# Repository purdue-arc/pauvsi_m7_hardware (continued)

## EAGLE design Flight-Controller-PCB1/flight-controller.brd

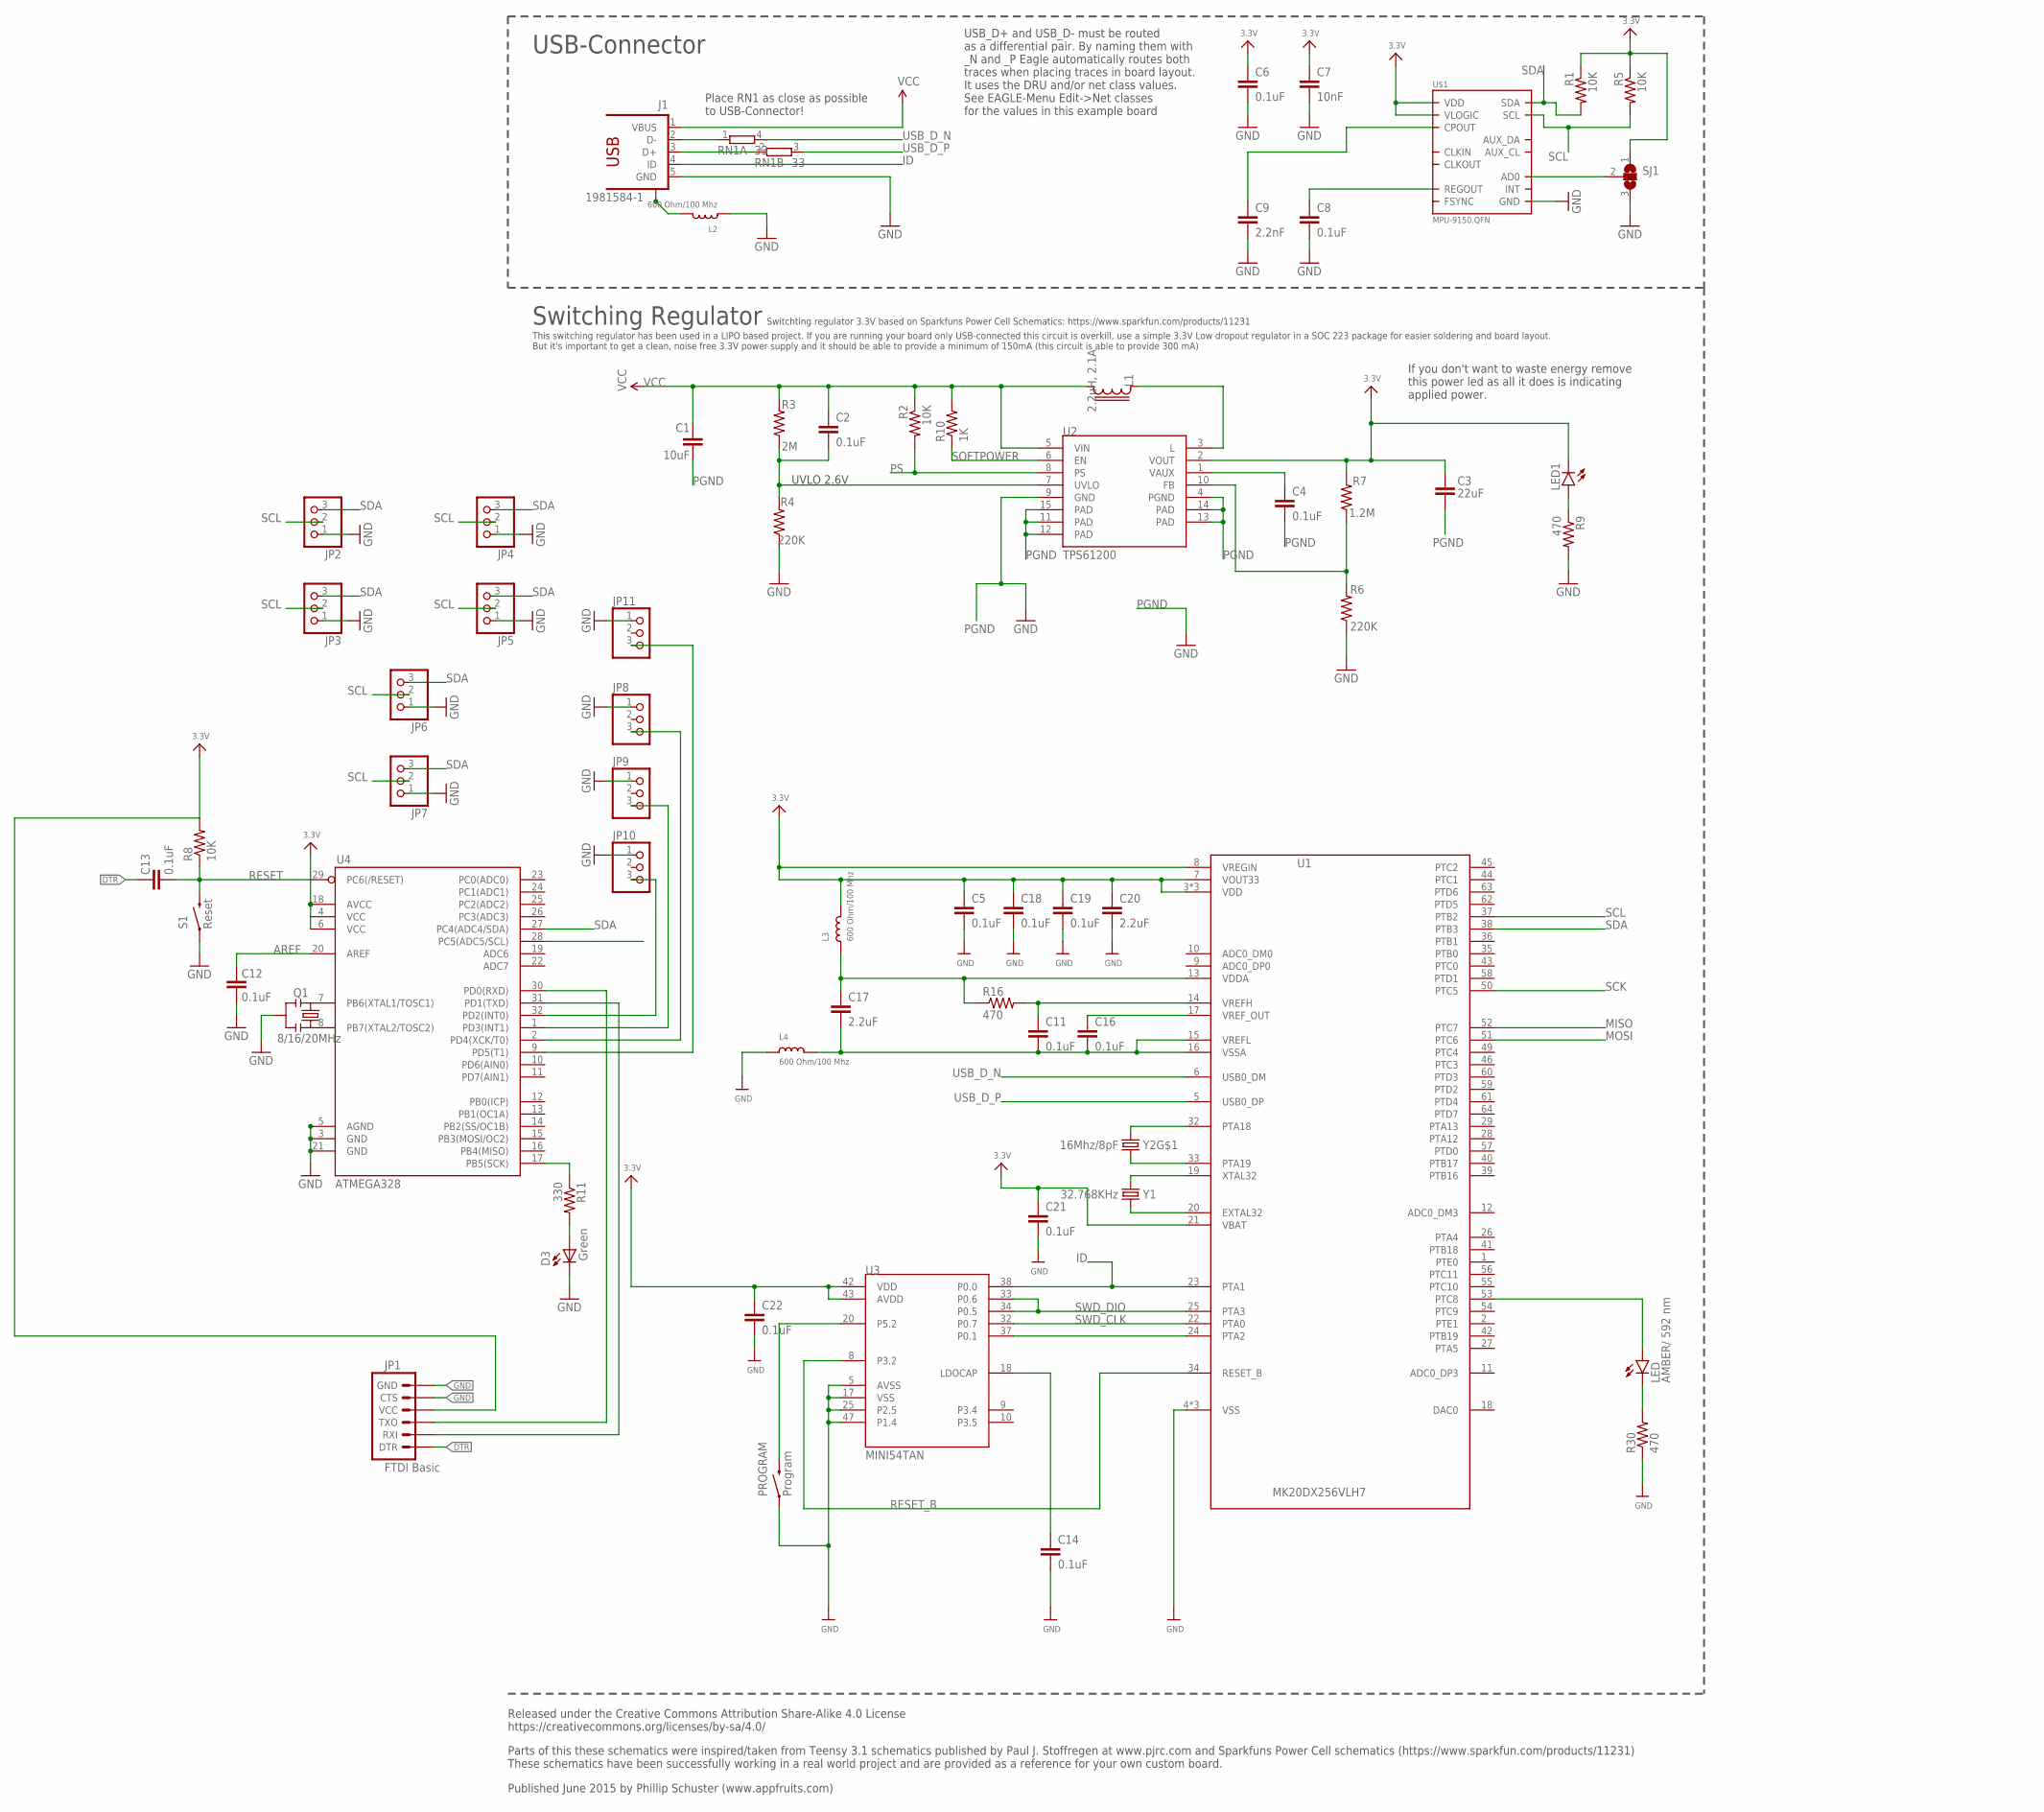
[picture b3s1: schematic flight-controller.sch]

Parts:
C1: 10uF; 0603-CAP
C2, C4, C5, C6, C8, C11, C12, C13, C14, C16, C18, C19, C21, C22: 0.1uF; 0603-CAP
C3: 22uF; 0603-CAP
C7: 10nF; 0603-CAP
C9: 2.2nF; 0603-CAP
C17, C20: 2.2uF; 0603-CAP
D3: Green; 0603-LED-ALT1
J1: 1981584-1; MPN ZX62-AB-5PA(11)
JP1: FTDI Basic; 1X06
JP2, JP3, JP4, JP5, JP6, JP7, JP8, JP9, JP10, JP11: PINHD-1X3; 1X03
L1: 2.2uH, 2.1A; LPS3015
L2, L3, L4: 600 Ohm/100 Mhz; 0805
LED: AMBER/ 592 nm; LED-0603
LED1: LED-GREEN; LED-0603
PROGRAM: Program; TACTILE-SWITCH-1101NE; MPN RS-282G05A3-SM RT
Q1: 8/16/20MHz; RESONATOR-SMD-1:1
R1, R2, R5, R8: 10K; 0603-RES
R3: 2M; 0603-RES
R4, R6: 220K; 0603-RES
R7: 1.2M; 0603-RES
R9, R16, R30: 470; 0603-RES
R10: 1K; 0603-RES
R11: 330; 0603-RES
RN1: 33; EXB34V; MPN EXB-34V330JV
S1: Reset; TACTILE-SWITCH-SMD-ALT01
SJ1: SJ2W; SJ_2
U1: MK20DX256VLH7; MPN MK20DX256VLH7
U2: TPS61200; QFN-10_PAD
U3: MINI54TAN
U4: ATMEGA328; TQFP32-08
U$1: MPU-9150.QFN; QFN.24.4X4
Y1: 32.768KHz; CRYSTAL-TXC-7A; MPN FC-255 32.7680K-A3
Y2: 16Mhz/8pF; CRYSTAL-SMD-5X3; MPN ECS-160-8-30B-CKM

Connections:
3.3V: C3.1, C5.1, C6.1, C7.1, C18.1, C19.1, C20.1, C21.1, C22.1, JP1.4 (VCC), L3.2, LED1.C, R1.1, R5.1, R7.2, R8.2, SJ1.1, U1.3 (VDD), U1.7 (VOUT33), U1.8 (VREGIN), U1.21 (VBAT), U1.30 (VDD), U1.48 (VDD), U2.2 (VOUT), U3.42 (VDD), U3.43 (AVDD), U4.4 (VCC), U4.6 (VCC), U4.18 (AVCC), U$1.3 (VDD), U$1.8 (VLOGIC), U$1.13 (VDD)
AREF: C12.2, U4.20 (AREF)
DTR: C13.2, JP1.1 (DTR)
FB: R6.2, R7.1, U2.10 (FB)
GND: C5.2, C6.2, C7.2, C8.2, C9.2, C12.1, C14.2, C18.2, C19.2, C20.2, C21.2, C22.2, D3.C, J1.5 (GND), JP1.5 (CTS), JP1.6 (GND), JP2.1, JP3.1, JP4.1, JP5.1, JP6.1, JP7.1, JP8.1, JP9.1, JP10.1, JP11.1, L2.1, L4.1, PROGRAM.P$1 (1), Q1.2, R4.1, R6.1, R9.2, R30.1, S1.1, S1.2 (1), SJ1.3, U1.4 (VSS), U1.31 (VSS), U1.47 (VSS), U3.5 (AVSS), U3.17 (VSS), U3.25 (P2.5), U3.47 (P1.4), U4.3 (GND), U4.5 (AGND), U4.21 (GND), U$1.15 (GND), U$1.17 (GND), U$1.18 (GND)
ID: J1.4 (ID), U1.23 (PTA1), U3.38 (P0.0)
MISO: U1.52 (PTC7)
MOSI: U1.51 (PTC6)
unnamed: LED1.A, R9.1
unnamed: L1.1, U2.3 (L)
unnamed: C9.1, U$1.20 (CPOUT)
unnamed: C8.1, U$1.10 (REGOUT)
unnamed: SJ1.2, U$1.9 (AD0)
unnamed: Q1.3, U4.8 (PB7(XTAL2/TOSC2))
unnamed: D3.A, R11.2
unnamed: Q1.1, U4.7 (PB6(XTAL1/TOSC1))
unnamed: JP1.3 (TXO), U4.30 (PD0(RXD))
unnamed: JP1.2 (RXI), U4.31 (PD1(TXD))
unnamed: JP10.3, U4.32 (PD2(INT0))
unnamed: LED.A, U1.53 (PTC8)
unnamed: JP9.3, U4.1 (PD3(INT1))
unnamed: JP8.3, U4.2 (PD4(XCK/T0))
unnamed: U1.24 (PTA2), U3.37 (P0.1)
unnamed: JP11.3, U4.9 (PD5(T1))
unnamed: LED.C, R30.2
unnamed: PROGRAM.P$2 (2), U3.20 (P5.2)
unnamed: C14.1, U3.18 (LDOCAP)
unnamed: U1.32 (PTA18), Y2.3 (2)
unnamed: U1.33 (PTA19), Y2.1
unnamed: U1.19 (XTAL32), Y1.P$2 (2)
unnamed: U1.20 (EXTAL32), Y1.P$1 (1)
NONE: R11.1, U4.17 (PB5(SCK))
PGND: C1.2, C3.2, C4.2, U2.4 (PGND), U2.9 (GND), U2.11 (PAD), U2.12 (PAD), U2.13 (PAD), U2.14 (PAD), U2.15 (PAD)
PS: R2.2, U2.8 (PS)
RESET: C13.1, R8.1, S1.3 (2), S1.4 (2), U4.29 (PC6(/RESET))
RESET_B: U1.34 (RESET_B), U3.8 (P3.2)
SCK: U1.50 (PTC5)
SCL: JP2.2, JP3.2, JP4.2, JP5.2, JP6.2, JP7.2, R5.2, U1.37 (PTB2), U4.28 (PC5(ADC5/SCL)), U$1.23 (SCL)
SDA: JP2.3, JP3.3, JP4.3, JP5.3, JP6.3, JP7.3, R1.2, U1.38 (PTB3), U4.27 (PC4(ADC4/SDA)), U$1.24 (SDA)
SOFTPOWER: R10.1, U2.6 (EN)
SWD_CLK: U1.22 (PTA0), U3.32 (P0.7)
SWD_DIO: U1.25 (PTA3), U3.33 (P0.6), U3.34 (P0.5)
USB_CON_N: J1.2 (D-), RN1.1
USB_CON_P: J1.3 (D+), RN1.2 (1)
USB_D_N: RN1.4 (2), U1.6 (USB0_DM)
USB_D_P: RN1.3 (2), U1.5 (USB0_DP)
USB_SHIELD: J1.S1, J1.S2, J1.S3, J1.S4, L2.2
UVLO: C2.2, R3.1, R4.2, U2.7 (UVLO)
VAUX: C4.1, U2.1 (VAUX)
VCC: C1.1, C2.1, J1.1 (VBUS), L1.2, R2.1, R3.2, R10.2, U2.5 (VIN)
VDDA: C17.1, L3.1, R16.1, U1.13 (VDDA)
VREFH: C11.1, R16.2, U1.14 (VREFH)
VREFL: C11.2, C16.2, C17.2, L4.2, U1.15 (VREFL), U1.16 (VSSA)
VREF_OUT: C16.1, U1.17 (VREF_OUT)

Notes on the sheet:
UVLO 2.6V
USB-Connector
Switching Regulator
Place RN1 as close as possible to USB-Connector!
If you don't want to waste energy remove this power led as all it does is indicating applied power.
USB_D+ and USB_D- must be routed as a differential pair. By naming them with _N and _P Eagle automatically routes both traces when placing traces in board layout. It uses the DRU and/or net class values. See EAGLE-Menu Edit->Net classes for the values in this example board
Released under the Creative Commons Attribution Share-Alike 4.0 License https://creativecommons.org/licenses/by-sa/4.0/
Parts of this these schematics were inspired/taken from Teensy 3.1 schematics published by Paul J. Stoffregen at www.pjrc.com and Sparkfuns Power Cell schematics (https://www.sparkfun.com/products/11231) These schematics have been successfully working in a real world project and are provided as a r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
Published June 2015 by Phillip Schuster (www.appfruits.com)
Switchting regulator 3.3V based on Sparkfuns Power Cell Schematics: https://www.sparkfun.com/products/11231
This switching regulator has been used in a LIPO based project. If you are running your board only USB-connected this circuit is overkill, use a simple 3.3V Low dropout regulator in a SOC 223 package for easier soldering and board layout. But it's important to get a clean, noise free 3.3V power sup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

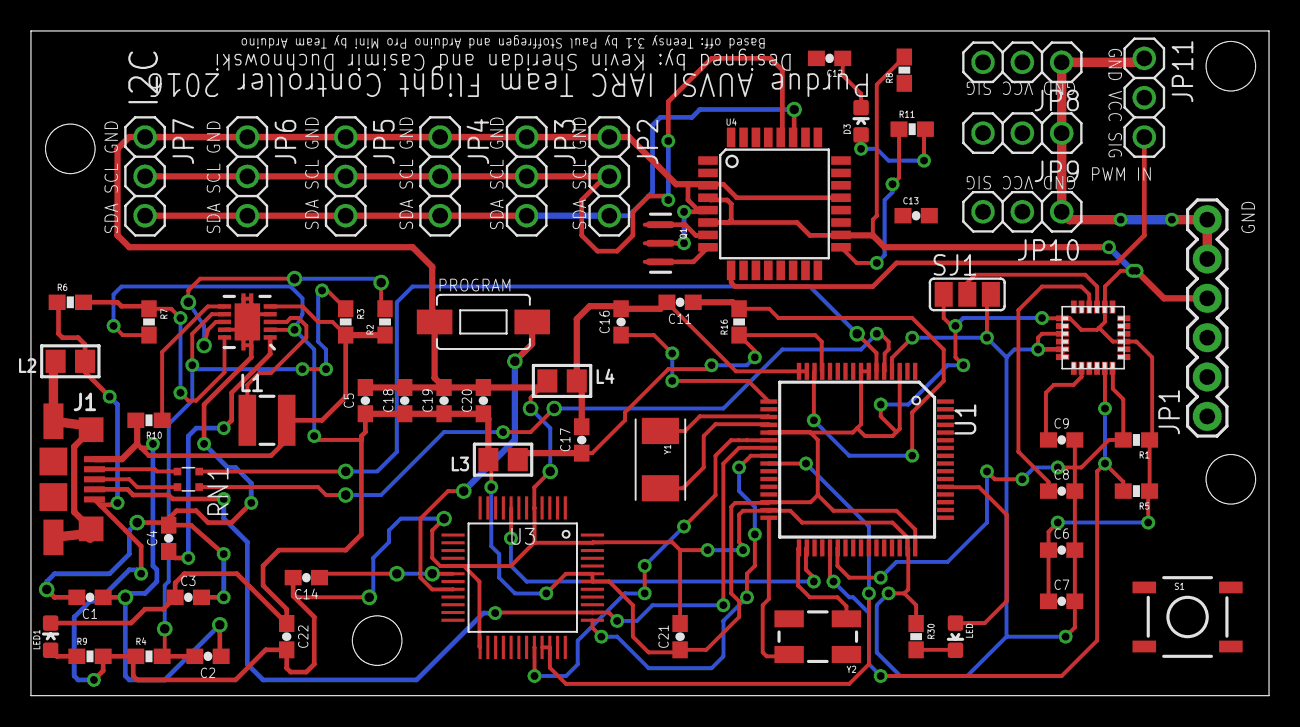
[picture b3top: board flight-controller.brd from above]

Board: 2 copper layers, 79.9 x 42.9 mm, 64 parts (0 on the bottom side), 51 nets.

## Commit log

2015-11-06 Created BRD files for version 1
2015-11-07 added brd
2015-11-08 fixed again
2015-11-08 added teensy library
2015-11-08 Added many eagle libraries so they can be shared
2015-11-08 started schematic
2015-11-15 added board libraries and board file
2015-11-15 Created teensy board file
2015-11-15 cleaned up the board but not done yet
2015-11-15 Flight controller arm laid out but no traces
2015-11-15 updated project file
2015-11-16 started board design over to make the traces shorter
2015-11-16 initial traces done
2015-11-18 started manually routing
2015-11-19 still routing
2015-11-19 continuing manual routing
2015-11-19 nearly finished routing
2015-11-19 finished traces
2015-11-20 added libraries and mph breakout example
2015-11-20 finished setting up my portion
2015-11-20 nearly finished routing the IMU
2015-11-20 finished teensy + imbue
2015-11-21 put up arduino mini pro example
2015-11-21 working on arduino pro mini
2015-11-21 still working on microcontroller
2015-11-21 most done microcontroller
2015-11-23 laying out board for final time
2015-11-23 finished for the night still need pwm and i2c
2015-11-26 making mods to pins
2015-11-26 wiring attempting
2015-11-26 Ready for manufacturer
2015-11-26 finished
2015-11-26 ordered
2015-11-27 testing fusion
2015-11-28 added the servo
2015-11-28 added the base mount but unfinished
2015-11-28 added the first step file
2015-11-29 finalized base mount
2015-12-05 test render
2015-12-05 added manufacture parts
2015-12-05 image
2016-01-17 put arduino on
2016-01-17 added ti lib
2016-01-23 bracket 1
2016-01-24 added ax-12 servo
2016-01-27 file not complete yet
2016-01-27 Roughdraft cad parts CAD parts
2016-02-03 added the hinge mount
2016-02-03 render
2016-02-07 stls added
2016-02-07 added nano ex
2016-02-22 firmware
2016-02-22 added aluminum plates
2016-02-22 more drawing
2016-02-27 added the flight controller code
2016-02-27 applied kaman filter and now have fuse IMU data
2016-02-29 added the teensy bob
2016-02-29 added the bed file for the bob
2016-02-29 decided to make this a dual teensy flight controller break out
2016-02-29 added the 10dof to the bob
2016-03-01 finishing up the pins
2016-03-01 finishing pins
2016-03-02 finished the schematic i think
2016-03-02 started the board layout
2016-03-02 routing wires
2016-03-02 finished routing
2016-03-02 Added the text to the board
2016-03-02 preparing to manufacture
2016-03-02 Added the mounting holes
2016-03-03 finished the board
2016-03-03 checked around the cpu
2016-03-03 added indicator led function
2016-03-30 change
2016-04-02 spacer
    spacers added
2016-04-26 Added the sol for the arm mounts
2016-04-29 Added the top protection Plate. Now printing
2016-05-01 Fixed the IMU axes
2016-05-01 Now the flight controller comminicates with ROS. It sends all relavent data.
2016-05-06 added sensor plate
2016-05-21 added stl
2016-05-21 added the servo back
2016-05-24 original solid parts for reference
2016-06-11 bracket 1
    finished bracket 1
2016-06-11 bracket 2
    bracket 2 finished
2016-07-24 the printer g code
2016-07-30 top bracket
2016-07-31 added bracket 4
2016-07-31 stiles
2016-07-31 the code for top and bottom bracket
2016-08-02 new bottom
2016-08-26 added the servo demo
2016-09-13 Merge remote-tracking branch 'origin/master'
    # Conflicts:
    #
    PAUVSIFlightControllerFirmware/PAUVSIFlightControllerFirmware/MPU9250Dri
    ver.ino
    #
    PAUVSIFlightControllerFirmware/PAUVSIFlightControllerFirmware/PAUVSIFlig
2016-09-13 commiting vpps
2016-09-13 added the arm files
2016-09-13 added the airframe files
2016-10-10 fixed direction
2017-02-08 new flight controller
2017-02-13 autoroutes the pub
2017-02-14 final pcb
2017-06-23 changed emu topics
2017-06-24 added two parts
2017-07-06 added models
2017-07-07 40% through main arm controller
2017-07-07 added torque
2017-07-21 added hardware
2017-07-22 made new motor mounts
